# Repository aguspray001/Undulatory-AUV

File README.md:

# Undulatory-AUV

## This is the visualization of undulatory AUV with undulatory fin:

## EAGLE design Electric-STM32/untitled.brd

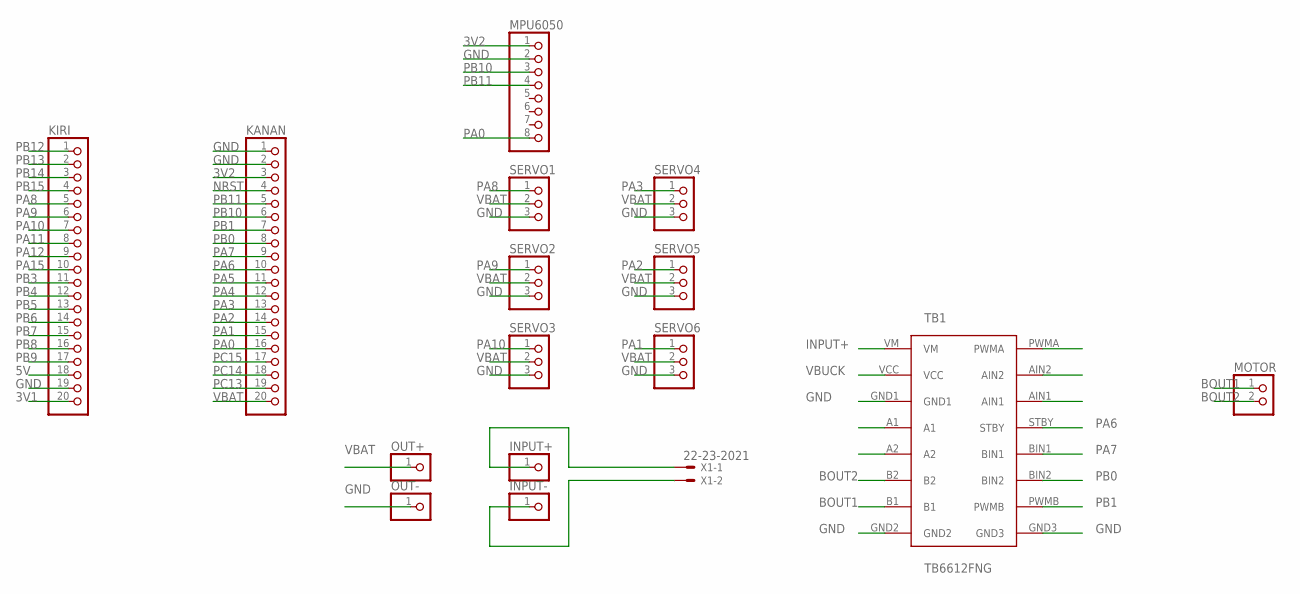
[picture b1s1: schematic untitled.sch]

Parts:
INPUT+: PINHD-1X1; 1X01
INPUT-: PINHD-1X1; 1X01
KANAN: PINHD-1X20; 1X20
KIRI: PINHD-1X20; 1X20
MOTOR: PINHD-1X2; 1X02
MPU6050: PINHD-1X8; 1X08
OUT+: PINHD-1X1; 1X01
OUT-: PINHD-1X1; 1X01
SERVO1, SERVO2, SERVO3, SERVO4, SERVO5, SERVO6: PINHD-1X3; 1X03
TB1: TB6612FNG
X1: 22-23-2021

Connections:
3V1: KIRI.20
3V2: KANAN.3, MPU6050.1
5V: KIRI.18
BOUT1: MOTOR.1, TB1.B1
BOUT2: MOTOR.2, TB1.B2
GND: KANAN.1, KANAN.2, KIRI.19, MPU6050.2, OUT-.1, SERVO1.3, SERVO2.3, SERVO3.3, SERVO4.3, SERVO5.3, SERVO6.3, TB1.GND1, TB1.GND2, TB1.GND3
INPUT+: TB1.VM
unnamed: INPUT+.1, X1.1
unnamed: INPUT-.1, X1.2
NRST: KANAN.4
PA0: KANAN.16, MPU6050.8
PA1: KANAN.15, SERVO6.1
PA2: KANAN.14, SERVO5.1
PA3: KANAN.13, SERVO4.1
PA4: KANAN.12
PA5: KANAN.11
PA6: KANAN.10, TB1.STBY
PA7: KANAN.9, TB1.BIN1
PA8: KIRI.5, SERVO1.1
PA9: KIRI.6, SERVO2.1
PA10: KIRI.7, SERVO3.1
PA11: KIRI.8
PA12: KIRI.9
PA15: KIRI.10
PB0: KANAN.8, TB1.BIN2
PB1: KANAN.7, TB1.PWMB
PB3: KIRI.11
PB4: KIRI.12
PB5: KIRI.13
PB6: KIRI.14
PB7: KIRI.15
PB8: KIRI.16
PB9: KIRI.17
PB10: KANAN.6, MPU6050.3
PB11: KANAN.5, MPU6050.4
PB12: KIRI.1
PB13: KIRI.2
PB14: KIRI.3
PB15: KIRI.4
PC13: KANAN.19
PC14: KANAN.18
PC15: KANAN.17
VBAT: KANAN.20, OUT+.1, SERVO1.2, SERVO2.2, SERVO3.2, SERVO4.2, SERVO5.2, SERVO6.2
VBUCK: TB1.VCC

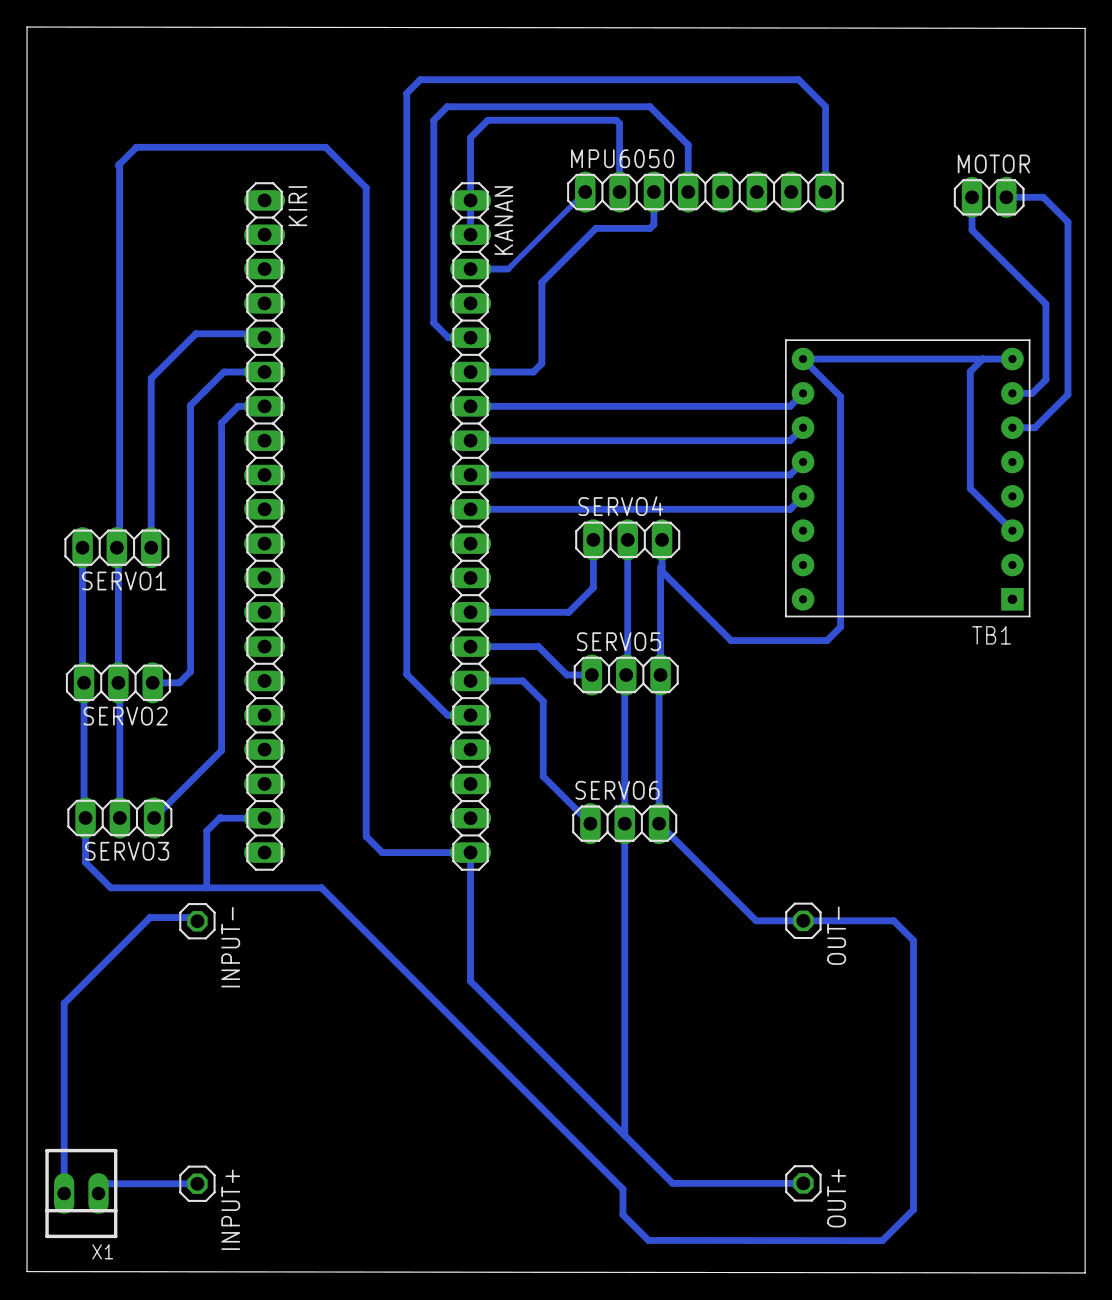
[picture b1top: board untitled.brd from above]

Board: 2 copper layers, 78.3 x 92.2 mm, 16 parts (0 on the bottom side), 20 nets.
